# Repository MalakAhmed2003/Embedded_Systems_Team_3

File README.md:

# Embedded Systems Course Project

The following repository contains different files of code for running a Maze Solver Robot that explores any given maze then generates the optimized path to run 
between the start and end points, then runs on this optimized path.
The Robot also has a bluetooth module that connects to the laptop and can be controlled through a custom website (which you can also filnd its python code here).
## Exploration and Optimized Path:
To get the Robot to explore and optimize the path taken to solve the maze:
1- Upload the Maze_Solver.ino code to the Robot Arduino 
2- Power up the system with ~ 9.4-9.6 V

### Hardware Architecture

### Code Architecture

## Running the Website:
To run the Website correctly and connect it to the Arduino through the HC-10 Bluetooth Module, follow the following steps:

1- Pair with HMSOFT.

2- Make sure it appears in the Bluetooth tab in the device manager.

3- In the Bluetooth tab in the Device Manager--> HMSOFT--> Details tab --> Bluetooth Device Address in the drop list --> (34:03:de:34:c7:9e)

4- Run hc10_bridge.py after changing the HC-10 known addresses to the address found in the device manager.

5- Run the Website.py

6- Change the serial print and read in Arduino code to be serial#, where # is based on the pins you are connecting your Hc-10 module to.

The Website should look like:

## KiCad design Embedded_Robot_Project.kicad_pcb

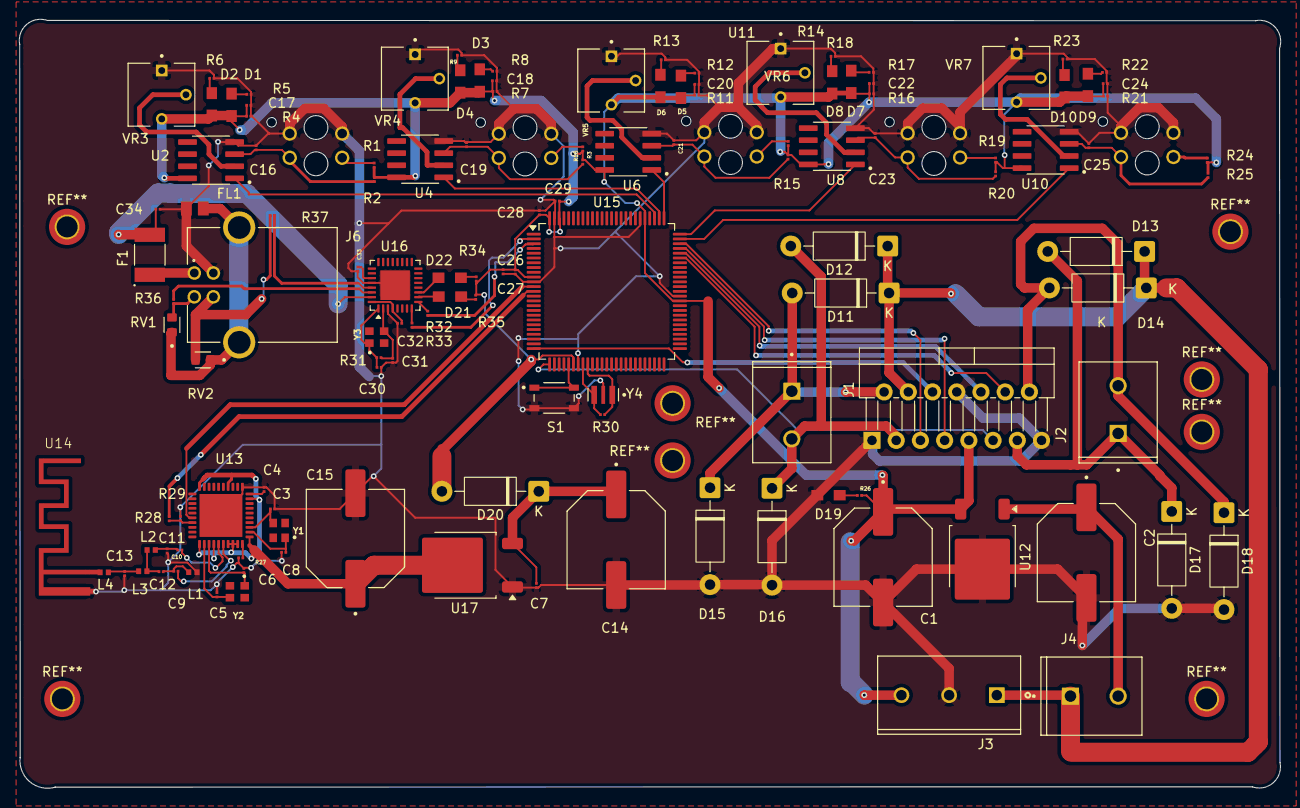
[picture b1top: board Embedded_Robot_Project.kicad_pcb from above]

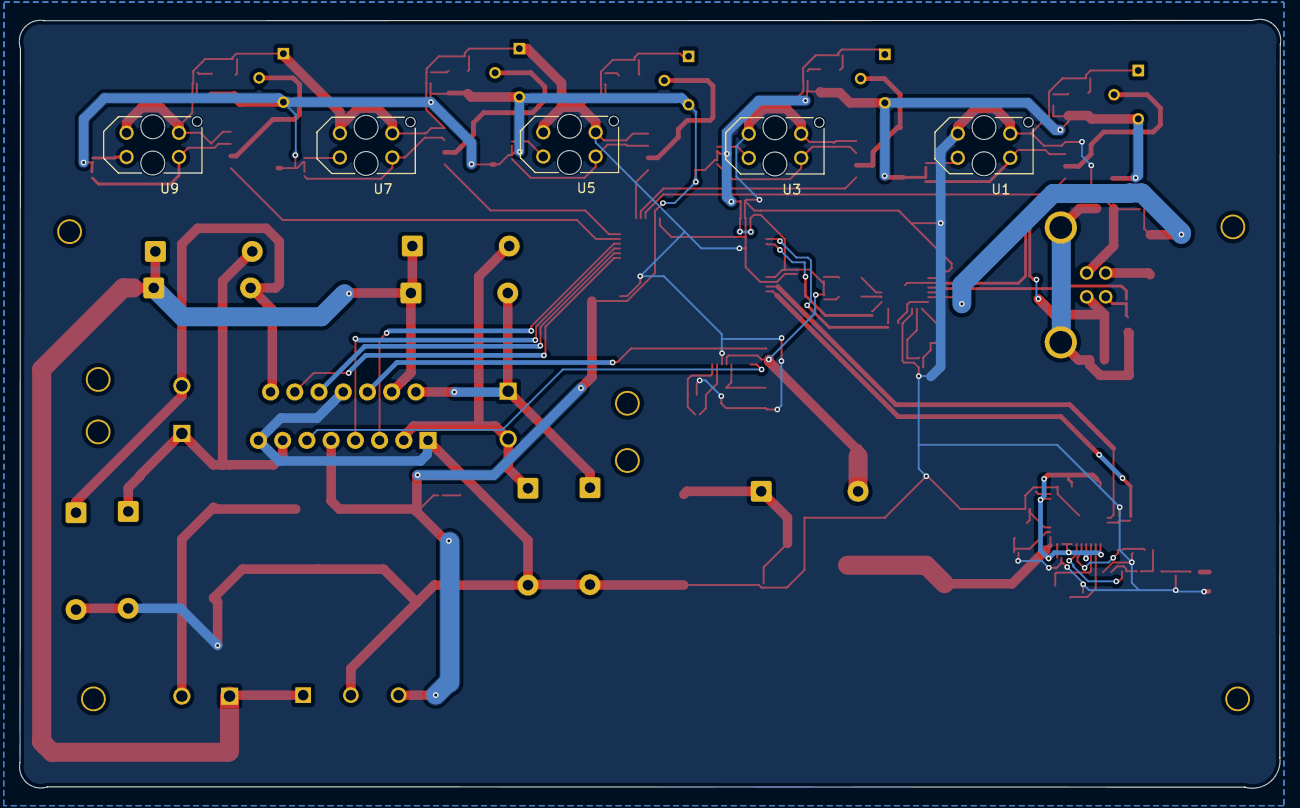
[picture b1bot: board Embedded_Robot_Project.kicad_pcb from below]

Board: 2 copper layers, 132.3 x 80.6 mm, 133 parts (5 on the bottom side), 85 nets.

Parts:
C1, C2: C_Polarized_Small_US; CAP_Polarized
C3, C4, C5, C6, C7, C8, C9, C10, C11, C12, C13, C16, C17, C18, C19, C20, C21, C22, C23, C24, C25, C26, C27, C28, C29, C30, C31, C32, C33, C34: GRM022R60G474ME15L; CAP_0402
C14, C15: C_Polarized; CAP_Polarized
D1, D2, D3, D4, D5, D6, D7, D8, D9, D10, D19, D21, D22: LED; LED_APT2012SURCK
D11, D12, D13, D14, D15, D16, D17, D18: 1N4007; D_DO-41_SOD81_P10.16mm_Horizontal
D20: 1N4001; D_DO-41_SOD81_P10.16mm_Horizontal
F1: MF-MSMF050-2; FUSM4632X85
FL1: BLM21SP111SH1D; BLM21
J1, J2, J4: Screw_Terminal_01x02; Screw_Connector_2
J3: Screw_Terminal_01x03; Screw_Connector_3
J6: TE_292304-1; USB_B
L1, L2, L3, L4: MLG1005S2N0BT000; INDC_01005
R1, R2, R3, R4, R5, R6, R7, R8, R9, R10, R11, R12, R13, R14, R15, R16, R17, R18, R19, R20, R21, R22, R23, R24, R25, R26, R27, R28, R29, R30, R31, R32, R33, R34, R35, R36, R37: RC0100FR-071KL; R_01005
RV1, RV2: CG0603MLC-05E; VARistor
S1: TS20-42-25-WT-160-SMT-TR; SW_Reset
U1, U3, U5, U7, U9: *; OPTO_TCRT5000
U2, U4, U6, U8, U10: LM393AD; LM393
U11: L298N; TO-220-15_P2.54x5.08mm_StaggerOdd_Lead4.58mm_Vertical
U12: KA78M05_TO252; TO-252-2
U13: CC2540F256RHAT; CC2540
U14: Antenna_BLE
U15: ATmega2560-16A; TQFP-100_14x14mm_P0.5mm
U16: ATmega16U2-M; QFN-32-1EP_5x5mm_P0.5mm_EP3.1x3.1mm
U17: NCP1117-3.3_TO252; TO-252-2
VR3, VR4, VR5, VR6, VR7: Variable_Resistor_3362P; Potontiometer
Y1, Y2, Y3: XTAL_Crystal_Oscillator; XTAL_Footprint
Y4: CSTCE16M0V53-R0; OSC_16M0V53_Arduino

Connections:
/Arduino_Mega/EN_A_Arduino: U11.6 (EnA), U15.25 (PB6)
/Arduino_Mega/EN_B_Arduino: U11.11 (EnB), U15.26 (PB7)
/Arduino_Mega/IN_1_Arduino: U11.5 (IN1), U15.73 (PA5)
/Arduino_Mega/IN_2_Arduino: U11.7 (IN2), U15.72 (PA6)
/Arduino_Mega/IN_3_Arduino: U11.10 (IN3), U15.71 (PA7)
/Arduino_Mega/IN_4_Arduino: U11.12 (IN4), U15.70 (PG2)
/Arduino_Mega/PE0: R33.1, U15.2 (PE0)
/Arduino_Mega/PE1: R32.1, U15.3 (PE1)
/Arduino_Mega/RX_2_Arduino: U13.16 (P0_3), U15.12 (PH0)
/Arduino_Mega/S_1_Arduino: U2.1 (1OUT), U15.78 (PA0)
/Arduino_Mega/S_2_Arduino: U4.1 (1OUT), U15.77 (PA1)
/Arduino_Mega/S_3_Arduino: U6.1 (1OUT), U15.76 (PA2)
/Arduino_Mega/S_4_Arduino: U8.1 (1OUT), U15.75 (PA3)
/Arduino_Mega/S_5_Arduino: U10.1 (1OUT), U15.74 (PA4)
/Arduino_Mega/TX_2_Arduino: R28.1, U15.13 (PH1)
/Arduino_Mega/USB_VCC: C34.2, F1.2, U16.31 (UVCC)
/BLE_HC_05/3.3V: C15.1, U13.4 (DVDD_USB), U13.10 (DVDD), U13.21 (AVDD), U13.24 (AVDD__1), U13.27 (AVDD__2), U13.28 (AVDD__3), U13.29 (AVDD__4), U13.31 (AVDD__5), U13.39 (DVDD__1), U17.2 (VO)
/BLE_HC_05/Pin_25: C10.1, U13.25 (RF_P)
/BLE_HC_05/Pin_26: C9.1, U13.26 (RF_N)
/BLE_HC_05/RX_BLE: R28.2, R29.1, U13.17 (P0_2)
/IR_Sensors/AO1: C16.2, R2.1, U1.COLL, U2.3 (1IN+)
/IR_Sensors/AO2: C19.2, R10.1, U3.COLL, U4.3 (1IN+)
/IR_Sensors/AO3: C21.2, R15.1, U5.COLL, U6.3 (1IN+)
/IR_Sensors/AO4: C23.2, R20.1, U7.COLL, U8.3 (1IN+)
/IR_Sensors/AO5: C25.2, R25.1, U9.COLL, U10.3 (1IN+)
GND: C1.2, C2.2, C3.1, C4.1, C5.1, C6.1, C7.1, C8.1, C11.1, C13.1, C14.2, C15.2, C16.1, C17.1, C18.1, C19.1, C20.1, C21.1, C22.1, C23.1, C24.1, C25.1, C26.2, C27.2, C28.2, C29.1, C30.2, C31.2, C32.1, C33.2, C34.1, D15.2 (A), D16.2 (A), D17.2 (A), D18.2 (A), D19.1 (K), FL1.2, J3.2, J6.4 (GND), L1.2, R4.1, R5.1, R6.1, R7.1, R8.1, R9.1, R11.1, R12.1, R13.1, R16.1, R17.1, R18.1, R21.1, R22.1, R23.1, R27.1, R29.2, S1.3, S1.4, U1.CATH, U1.E, U2.4 (GND), U3.CATH, U3.E, U4.4 (GND), U5.CATH, U5.E, U6.4 (GND), U7.CATH, U7.E, U8.4 (GND), U9.CATH, U9.E, U10.4 (GND), U11.1 (SENSE_A), U11.8 (GND), U11.15 (SENSE_B), U12.2 (GND), U13.1 (DGND_USB), U13.EXP (GND), U14.2, U15.11 (GND), U15.32 (GND), U15.62 (GND), U15.81 (GND), U15.99 (GND), U16.3 (GND), U16.28 (UGND), U16.33 (GND), U17.1 (GND), VR3.1, VR4.1, VR5.1, VR6.1, VR7.1, Y4.2
unnamed: C10.2, C11.2, L2.1
unnamed: C9.2, C12.1, L1.1
unnamed: C12.2, L2.2, L3.1
unnamed: C13.2, L3.2, L4.1
unnamed: D1.1 (K), R5.2
unnamed: D2.1 (K), R6.2
unnamed: D3.1 (K), R8.2
unnamed: D4.1 (K), R9.2
unnamed: D5.1 (K), R12.2
unnamed: D6.1 (K), R13.2
unnamed: D7.1 (K), R17.2
unnamed: D8.1 (K), R18.2
unnamed: D9.1 (K), R22.2
unnamed: D10.1 (K), R23.2
unnamed: D11.2 (A), D15.1 (K), J1.1, U11.2 (OUT1)
unnamed: D12.2 (A), D16.1 (K), J1.2, U11.3 (OUT2)
unnamed: D13.2 (A), D17.1 (K), J2.1, U11.13 (OUT3)
unnamed: D14.2 (A), D18.1 (K), J2.2, U11.14 (OUT4)
unnamed: D19.2 (A), R26.1
unnamed: C7.2, C14.1, D20.1 (K), U17.3 (VI)
unnamed: D21.2 (A), R35.2
unnamed: D21.1 (K), U16.10 (PD4)
unnamed: D22.2 (A), R34.2
unnamed: D22.1 (K), U16.11 (PD5)
unnamed: C2.1, J4.2, U12.1 (VI)
unnamed: J6.3 (D+), R37.2, RV2.2
unnamed: J6.2 (D-), R36.2, RV1.2
unnamed: FL1.1, J6.S1 (SHIELD), J6.S2 (SHIELD__1), RV1.1, RV2.1
unnamed: F1.1, J6.1 (VBUS)
unnamed: L4.2, U14.1
unnamed: R1.1, U1.A
unnamed: R3.1, U3.A
unnamed: R14.1, U5.A
unnamed: R19.1, U7.A
unnamed: R24.1, U9.A
unnamed: U2.2 (1IN-), VR3.2
unnamed: U4.2 (1IN-), VR4.2
unnamed: U6.2 (1IN-), VR5.2
unnamed: U8.2 (1IN-), VR6.2
unnamed: U10.2 (1IN-), VR7.2
unnamed: C4.2, U13.40 (DCOUPL)
unnamed: C3.2, U13.33 (P2_3), Y1.3
unnamed: C8.2, U13.32 (P2_4), Y1.1
unnamed: R27.2, U13.30 (RBIAS)
unnamed: C5.2, U13.22 (XOSC_Q1), Y2.3
unnamed: C6.2, U13.23 (XOSC_Q2), Y2.1
unnamed: R30.2, U15.34 (XTAL1), Y4.1
unnamed: R30.1, U15.33 (XTAL2), Y4.3
unnamed: S1.1, S1.2, U15.30 (~RESET)
unnamed: C32.2, U16.4 (VCC), U16.32 (AVCC)
unnamed: R37.1, U16.29 (D+)
unnamed: R36.1, U16.30 (D-)
unnamed: C31.1, R31.1, U16.2 (PC0/XTAL2), Y3.3
unnamed: R33.2, U16.8 (PD2)
unnamed: R32.2, U16.9 (PD3)
unnamed: C33.1, U16.27 (UCAP)
unnamed: C30.1, R31.2, U16.1 (XTAL1), Y3.1
Power_In: D11.1 (K), D12.1 (K), D13.1 (K), D14.1 (K), J3.1, J4.1, U11.4 (Vs)
VCC: C1.1, C17.2, C18.2, C20.2, C22.2, C24.2, C26.1, C27.1, C28.1, C29.2, D1.2 (A), D2.2 (A), D3.2 (A), D4.2 (A), D5.2 (A), D6.2 (A), D7.2 (A), D8.2 (A), D9.2 (A), D10.2 (A), D20.2 (A), J3.3, R1.2, R2.2, R3.2, R4.2, R7.2, R10.2, R11.2, R14.2, R15.2, R16.2, R19.2, R20.2, R21.2, R24.2, R25.2, R26.2, R34.1, R35.1, U2.8 (VCC), U4.8 (VCC), U6.8 (VCC), U8.8 (VCC), U10.8 (VCC), U11.9 (Vss), U12.3 (VO), U15.10 (VCC), U15.31 (VCC), U15.61 (VCC), U15.80 (VCC), U15.98 (AREF), U15.100 (AVCC), VR3.3, VR4.3, VR5.3, VR6.3, VR7.3

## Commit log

2026-04-16 Create hc10_bridge
2026-04-16 Rename hc10_bridge to hc10_bridge.py
2026-05-14 Rename Embedded_Robot_Project_final.zip to Schematics_and_PCB_final.zip
